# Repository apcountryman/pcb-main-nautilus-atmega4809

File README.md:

# pcb-main-nautilus-atmega4809

A Microchip ATmega4809 based mainboard PCB that uses a form factor similar to the Arduino
Uno Rev3.

## Obtaining the Source Code
HTTPS:
```shell
git clone --recurse-submodules https://github.com/apcountryman/pcb-main-nautilus-atmega4809.git
```
SSH:
```shell
git clone --recurse-submodules git@github.com:apcountryman/pcb-main-nautilus-atmega4809.git
```

## Board Setup
The board setup uses OSH Park's 4 layer board stackup and design rules which can be found
at https://docs.oshpark.com/services/ and https://docs.oshpark.com/services/four-layer/.

## Usage
This repository's Git `pre-commit` hook script is the simplest way to test this project
during development.
See the `pre-commit` script's help text for usage details.
```shell
./git/hooks/pre-commit --help
```

Additional checks, such as static analysis, are performed by this project's GitHub Actions
CI workflow.

## Versioning
`pcb-main-nautilus-atmega4809` uses [Semantic Versioning
2.0.0](https://semver.org/spec/v2.0.0.html).
Version tags are prefixed with a `v`.

## Workflow
`pcb-main-nautilus-atmega4809` uses the [GitHub
flow](https://guides.github.com/introduction/flow/) workflow.

## Git Hooks
To install this repository's Git hooks, execute the `install` script located in the
`git/hooks` directory.
See the `install` script's help text for usage details.
```shell
./git/hooks/install --help
```

## Code of Conduct
`pcb-main-nautilus-atmega4809` has adopted the Contributor Covenant 2.0 code of conduct.
For more information, [see the `CODE_OF_CONDUCT.md` file in this
repository](CODE_OF_CONDUCT.md).

## Contributing
If you are interested in contributing to `pcb-main-nautilus-atmega4809`, please [read the
`CONTRIBUTING.md` file in this repository](CONTRIBUTING.md).

## Authors
- Andrew Countryman

## License
For licensing information, [see the `LICENSE.md` file in this repository](LICENSE.md).

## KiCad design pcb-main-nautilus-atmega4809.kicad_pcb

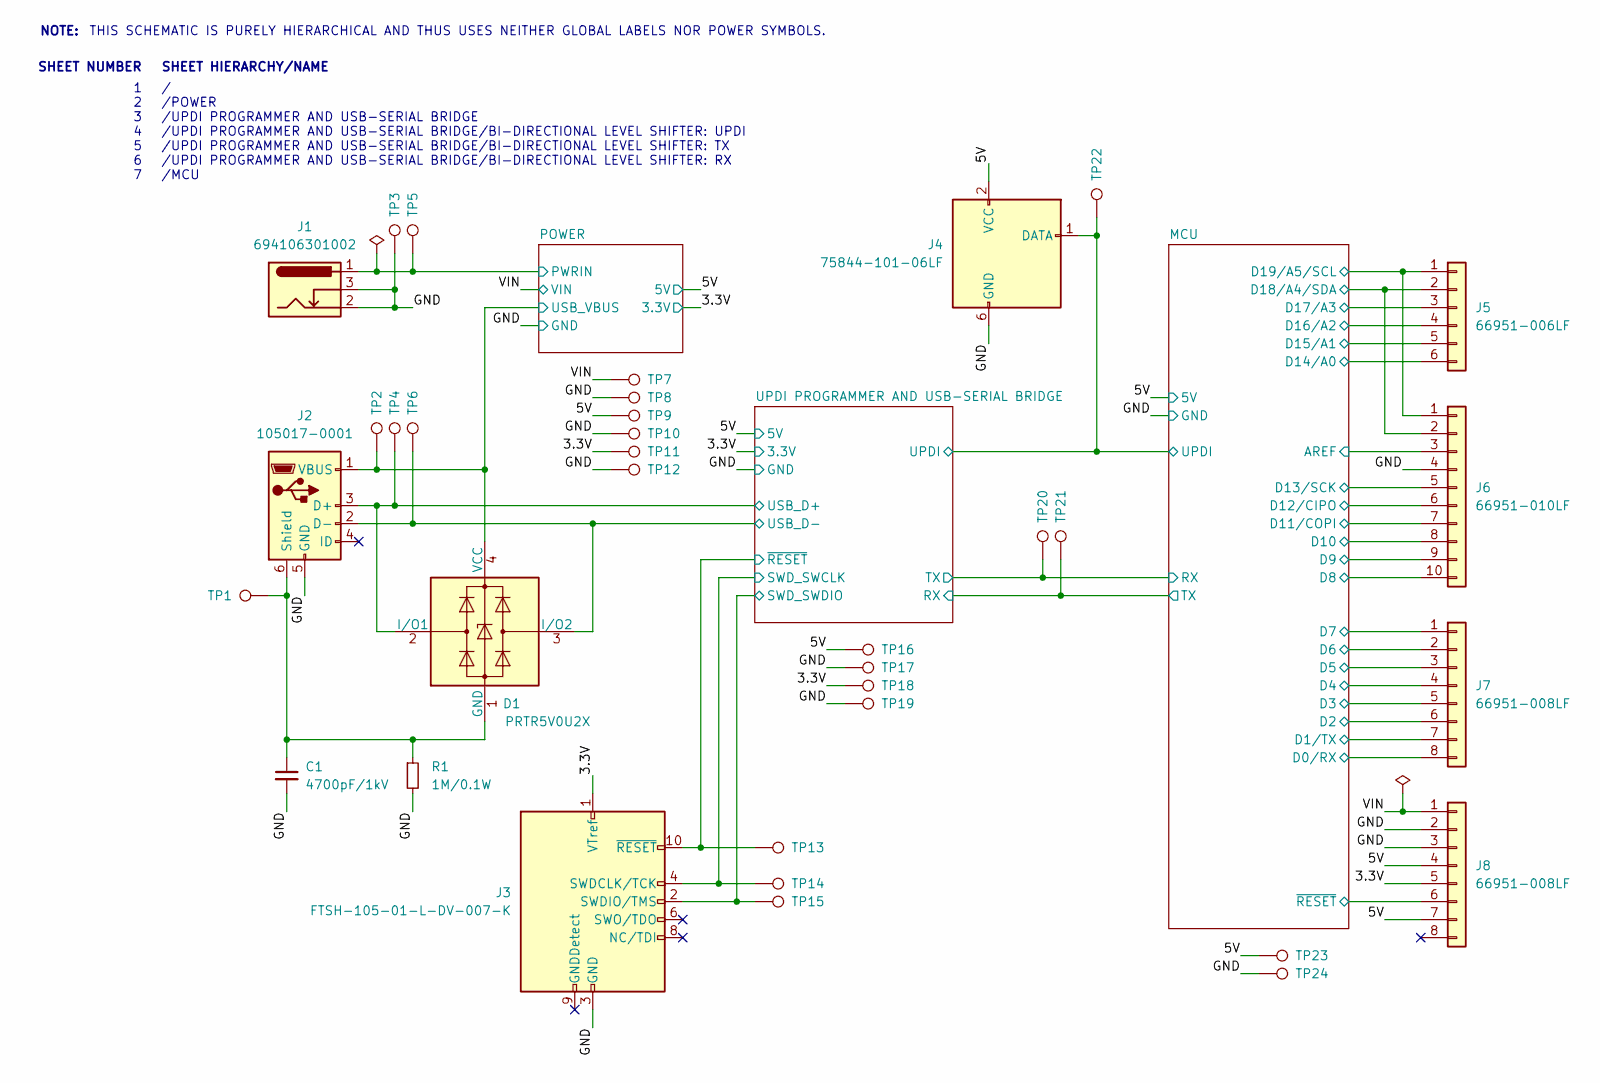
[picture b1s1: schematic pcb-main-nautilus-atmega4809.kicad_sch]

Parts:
C1: 4700pF/1kV; C_0805_2012Metric_Pad1.18x1.45mm_HandSolder; Manufacturer Part Number C0805V472KDRAC; Digi-Key Part Number 399-C0805V472KDRAC7800CT-ND
D1: PRTR5V0U2X; SOT-143; Manufacturer Part Number PRTR5V0U2X; Digi-Key Part Number 1727-3884-1-ND
J1: 694106301002; BarrelJack_Wuerth_6941xx301002; Manufacturer Part Number 694106301002; Digi-Key Part Number 732-5930-ND
J2: 105017-0001; USB_Micro-B_Molex-105017-0001; Manufacturer Part Number 105017-0001; Digi-Key Part Number WM1399CT-ND
J3: FTSH-105-01-L-DV-007-K; PinHeader_2x05_P1.27mm_Vertical_SMD; Manufacturer Part Number FTSH-105-01-L-DV-007-K; Digi-Key Part Number SAM9438-ND
J4: 75844-101-06LF; PinHeader_2x03_P2.54mm_Vertical; Manufacturer Part Number 75844-101-06LF; Digi-Key Part Number 609-75844-101-06LF-ND
J5: 66951-006LF; PinHeader_1x06_P2.54mm_Vertical; Manufacturer Part Number 66951-006LF; Digi-Key Part Number 609-2236-ND
J6: 66951-010LF; PinHeader_1x10_P2.54mm_Vertical; Manufacturer Part Number 66951-010LF; Digi-Key Part Number 609-2240-ND
J7, J8: 66951-008LF; PinHeader_1x08_P2.54mm_Vertical; Manufacturer Part Number 66951-008LF; Digi-Key Part Number 609-2238-ND
R1: 1M/0.1W; R_0603_1608Metric_Pad0.98x0.95mm_HandSolder; Manufacturer Part Number ERJ-3EKF1004; Digi-Key Part Number P1.00MHCT-ND
TP1, TP2, TP3, TP4, TP5, TP6, TP7, TP8, TP9, TP10, TP11, TP12, TP13, TP14, TP15, TP16, TP17, TP18, TP19, TP20, TP21, TP22, TP23, TP24: TestPoint; TestPoint_Pad_D1.0mm

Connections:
/3.3V: J3.1 (VTref), J8.5, TP11.1, TP18.1; also elsewhere on the board
/5V: J4.2 (VCC), J8.4, J8.7, TP9.1, TP16.1, TP23.1; also elsewhere on the board
/GND: C1.2, J1.2, J1.3, J2.5 (GND), J3.3 (GND), J3.5 (GND), J4.6 (GND), J6.4, J8.2, J8.3, R1.2, TP3.1, TP8.1, TP10.1, TP12.1, TP17.1, TP19.1, TP24.1; also elsewhere on the board
/MCU/AREF: J6.3; also elsewhere on the board
/MCU/D0/RX: J7.8; also elsewhere on the board
/MCU/D1/TX: J7.7; also elsewhere on the board
/MCU/D2: J7.6; also elsewhere on the board
/MCU/D3: J7.5; also elsewhere on the board
/MCU/D4: J7.4; also elsewhere on the board
/MCU/D5: J7.3; also elsewhere on the board
/MCU/D6: J7.2; also elsewhere on the board
/MCU/D7: J7.1; also elsewhere on the board
/MCU/D8: J6.10; also elsewhere on the board
/MCU/D9: J6.9; also elsewhere on the board
/MCU/D10: J6.8; also elsewhere on the board
/MCU/D11/COPI: J6.7; also elsewhere on the board
/MCU/D12/CIPO: J6.6; also elsewhere on the board
/MCU/D13/SCK: J6.5; also elsewhere on the board
/MCU/D14/A0: J5.6; also elsewhere on the board
/MCU/D15/A1: J5.5; also elsewhere on the board
/MCU/D16/A2: J5.4; also elsewhere on the board
/MCU/D17/A3: J5.3; also elsewhere on the board
/MCU/D18/A4/SDA: J5.2, J6.2; also elsewhere on the board
/MCU/D19/A5/SCL: J5.1, J6.1; also elsewhere on the board
/MCU/RX: TP20.1; also elsewhere on the board
/MCU/TX: TP21.1; also elsewhere on the board
/MCU/UPDI: J4.1 (DATA), TP22.1; also elsewhere on the board
/MCU/~RESET: J8.6; also elsewhere on the board
/POWER/PWRIN: J1.1, TP5.1; also elsewhere on the board
/POWER/USB_VBUS: D1.4 (VCC), J2.1 (VBUS), TP2.1; also elsewhere on the board
/UPDI PROGRAMMER AND USB-SERIAL BRIDGE/SWD_SWCLK: J3.4 (SWDCLK/TCK), TP14.1; also elsewhere on the board
/UPDI PROGRAMMER AND USB-SERIAL BRIDGE/SWD_SWDIO: J3.2 (SWDIO/TMS), TP15.1; also elsewhere on the board
/UPDI PROGRAMMER AND USB-SERIAL BRIDGE/USB_D+: D1.2 (I/O1), J2.3 (D+), TP4.1; also elsewhere on the board
/UPDI PROGRAMMER AND USB-SERIAL BRIDGE/USB_D-: D1.3 (I/O2), J2.2 (D-), TP6.1; also elsewhere on the board
/UPDI PROGRAMMER AND USB-SERIAL BRIDGE/~RESET: J3.10 (~RESET), TP13.1; also elsewhere on the board
/VIN: J8.1, TP7.1; also elsewhere on the board
unnamed: C1.1, D1.1 (GND), J2.6 (Shield), R1.1, TP1.1

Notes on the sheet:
/ /POWER /UPDI PROGRAMMER AND USB-SERIAL BRIDGE /UPDI PROGRAMMER AND USB-SERIAL BRIDGE/BI-DIRECTIONAL LEVEL SHIFTER: UPDI /UPDI PROGRAMMER AND USB-SERIAL BRIDGE/BI-DIRECTIONAL LEVEL SHIFTER: TX /UPDI PROGRAMMER AND USB-SERIAL BRIDGE/BI-DIRECTIONAL LEVEL SHIFTER: RX /MCU
SHEET HIERARCHY/NAME
1 2 3 4 5 6 7
THIS SCHEMATIC IS PURELY HIERARCHICAL AND THUS USES NEITHER GLOBAL LABELS NOR POWER SYMBOLS.
SHEET NUMBER
NOTE:

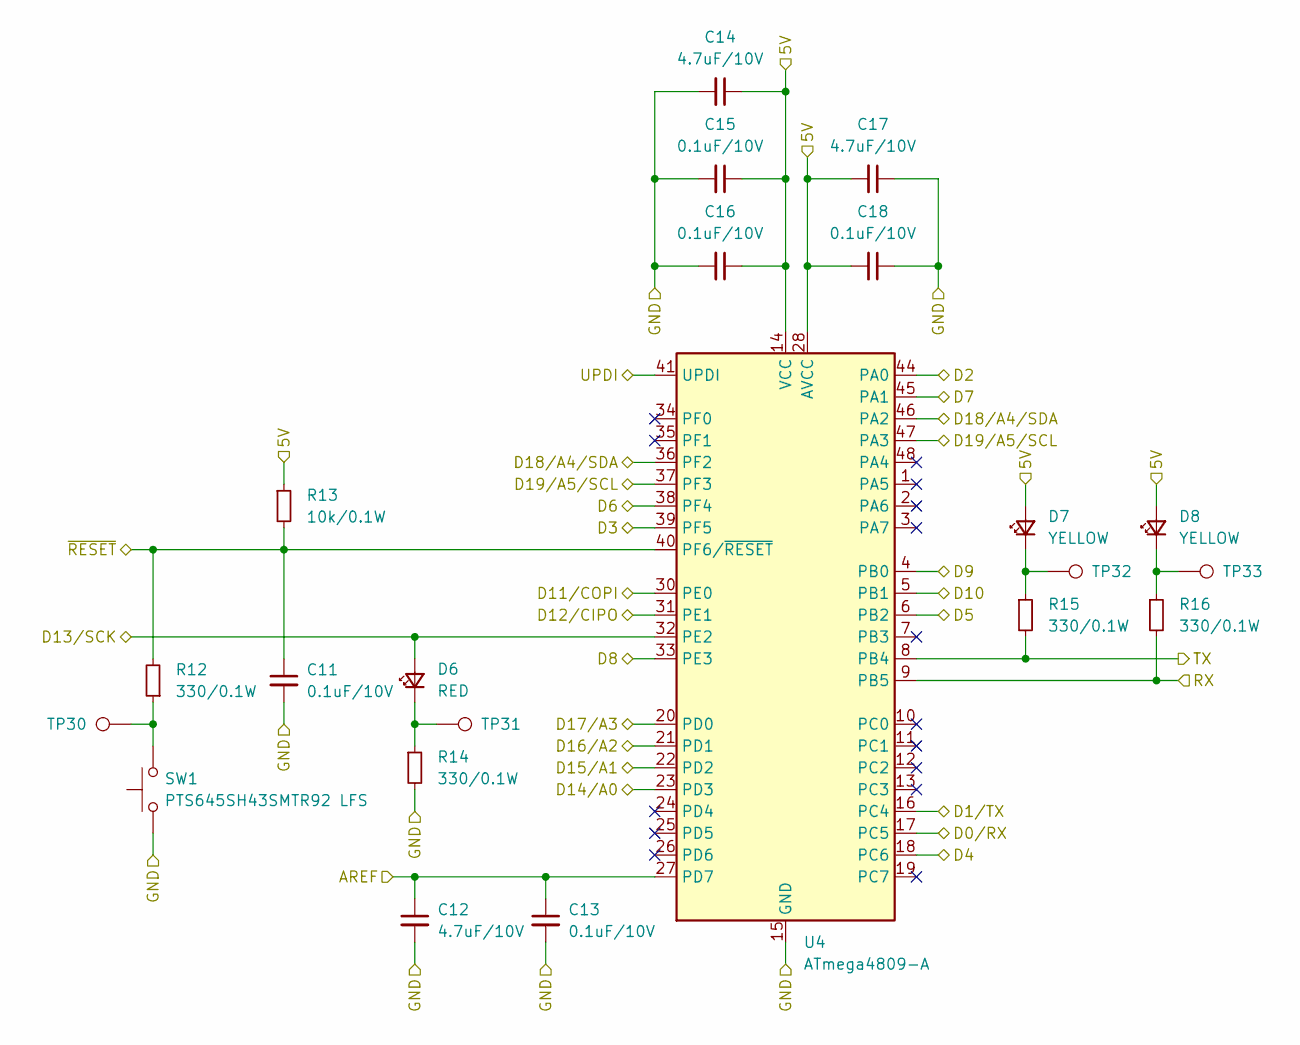
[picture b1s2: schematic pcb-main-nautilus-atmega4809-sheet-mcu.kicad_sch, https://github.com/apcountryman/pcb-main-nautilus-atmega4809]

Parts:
C11, C13, C15, C16, C18: 0.1uF/10V; C_0603_1608Metric_Pad1.08x0.95mm_HandSolder; Manufacturer Part Number C0603C104M8RAC; Digi-Key Part Number 399-C0603C104M8RAC7867CT-ND
C12, C14, C17: 4.7uF/10V; C_0603_1608Metric_Pad1.08x0.95mm_HandSolder; Manufacturer Part Number C0603C475M8PAC; Digi-Key Part Number 399-C0603C475M8PAC7867CT-ND
D6: RED; LED_0603_1608Metric_Pad1.05x0.95mm_HandSolder; Manufacturer Part Number LTST-C190KRKT; Digi-Key Part Number 160-1436-1-ND
D7, D8: YELLOW; LED_0603_1608Metric_Pad1.05x0.95mm_HandSolder; Manufacturer Part Number LTST-C190KSKT; Digi-Key Part Number 160-1437-1-ND
R12, R14, R15, R16: 330/0.1W; R_0603_1608Metric_Pad0.98x0.95mm_HandSolder; Manufacturer Part Number ERJ-3EKF3300; Digi-Key Part Number P330HCT-ND
R13: 10k/0.1W; R_0603_1608Metric_Pad0.98x0.95mm_HandSolder; Manufacturer Part Number ERJ-3EKF1002; Digi-Key Part Number P10.0KHCT-ND
SW1: PTS645SH43SMTR92 LFS; SW_Push_1P1T_NO_6x6mm_H9.5mm; Manufacturer Part Number PTS645SH43SMTR92 LFS; Digi-Key Part Number CKN11907CT-ND
TP30, TP31, TP32, TP33: TestPoint; TestPoint_Pad_D1.0mm
U4: ATmega4809-A; TQFP-48_7x7mm_P0.5mm; Manufacturer Part Number ATMEGA4809-AU; Digi-Key Part Number 150-ATMEGA4809-AURCT-ND

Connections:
/5V: C14.1, C15.1, C16.1, C17.2, C18.2, D7.2 (A), D8.2 (A), R13.1, U4.14 (VCC), U4.28 (AVCC), U4.42 (VCC); also elsewhere on the board
/GND: C11.2, C12.2, C13.2, C14.2, C15.2, C16.2, C17.1, C18.1, R14.2, SW1.1, U4.15 (GND), U4.29 (GND), U4.43 (GND); also elsewhere on the board
/MCU/AREF: C12.1, C13.1, U4.27 (PD7); also elsewhere on the board
/MCU/D0/RX: U4.17 (PC5); also elsewhere on the board
/MCU/D1/TX: U4.16 (PC4); also elsewhere on the board
/MCU/D2: U4.44 (PA0); also elsewhere on the board
/MCU/D3: U4.39 (PF5); also elsewhere on the board
/MCU/D4: U4.18 (PC6); also elsewhere on the board
/MCU/D5: U4.6 (PB2); also elsewhere on the board
/MCU/D6: U4.38 (PF4); also elsewhere on the board
/MCU/D7: U4.45 (PA1); also elsewhere on the board
/MCU/D8: U4.33 (PE3); also elsewhere on the board
/MCU/D9: U4.4 (PB0); also elsewhere on the board
/MCU/D10: U4.5 (PB1); also elsewhere on the board
/MCU/D11/COPI: U4.30 (PE0); also elsewhere on the board
/MCU/D12/CIPO: U4.31 (PE1); also elsewhere on the board
/MCU/D13/SCK: D6.2 (A), U4.32 (PE2); also elsewhere on the board
/MCU/D14/A0: U4.23 (PD3); also elsewhere on the board
/MCU/D15/A1: U4.22 (PD2); also elsewhere on the board
/MCU/D16/A2: U4.21 (PD1); also elsewhere on the board
/MCU/D17/A3: U4.20 (PD0); also elsewhere on the board
/MCU/D18/A4/SDA: U4.36 (PF2), U4.46 (PA2); also elsewhere on the board
/MCU/D19/A5/SCL: U4.37 (PF3), U4.47 (PA3); also elsewhere on the board
/MCU/RX: R16.2, U4.9 (PB5); also elsewhere on the board
/MCU/TX: R15.2, U4.8 (PB4); also elsewhere on the board
/MCU/UPDI: U4.41 (UPDI); also elsewhere on the board
/MCU/~RESET: C11.1, R12.2, R13.2, U4.40 (PF6/~RESET); also elsewhere on the board
unnamed: D6.1 (K), R14.1, TP31.1
unnamed: D7.1 (K), R15.1, TP32.1
unnamed: D8.1 (K), R16.1, TP33.1
unnamed: R12.1, SW1.2, TP30.1

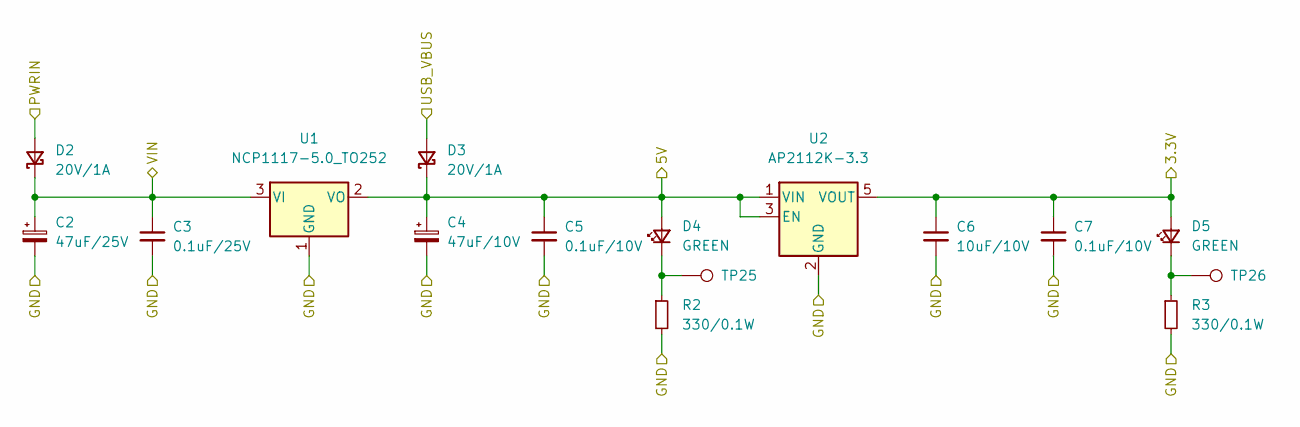
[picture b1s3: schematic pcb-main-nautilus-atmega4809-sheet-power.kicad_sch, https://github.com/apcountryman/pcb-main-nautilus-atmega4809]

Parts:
C2: 47uF/25V; CP_Elec_6.3x7.7; Manufacturer Part Number EEEHC1E470XP; Digi-Key Part Number PCE3753CT-ND
C3: 0.1uF/25V; C_0603_1608Metric_Pad1.08x0.95mm_HandSolder; Manufacturer Part Number C0603C104M3RAC; Digi-Key Part Number 399-C0603C104M3RAC7867CT-ND
C4: 47uF/10V; CP_Elec_4x5.8; Manufacturer Part Number EEEFN1A470UR; Digi-Key Part Number 10-EEE-FN1A470URCT-ND
C5, C7: 0.1uF/10V; C_0603_1608Metric_Pad1.08x0.95mm_HandSolder; Manufacturer Part Number C0603C104M8RAC; Digi-Key Part Number 399-C0603C104M8RAC7867CT-ND
C6: 10uF/10V; C_0603_1608Metric_Pad1.08x0.95mm_HandSolder; Manufacturer Part Number C0603C106M8PAC; Digi-Key Part Number 399-14945-1-ND
D2, D3: 20V/1A; D_SOD-123F; Manufacturer Part Number MBR120LSF; Digi-Key Part Number MBR120LSFT3GOSCT-ND
D4, D5: GREEN; LED_0603_1608Metric_Pad1.05x0.95mm_HandSolder; Manufacturer Part Number LTST-C190KGKT; Digi-Key Part Number 160-1435-1-ND
R2, R3: 330/0.1W; R_0603_1608Metric_Pad0.98x0.95mm_HandSolder; Manufacturer Part Number ERJ-3EKF3300; Digi-Key Part Number P330HCT-ND
TP25, TP26: TestPoint; TestPoint_Pad_D1.0mm
U1: NCP1117-5.0_TO252; TO-252-2; Manufacturer Part Number NCP1117DT50; Digi-Key Part Number NCP1117DT50RKGOSCT-ND
U2: AP2112K-3.3; SOT-23-5; Manufacturer Part Number AP2112K-3.3TRG1; Digi-Key Part Number AP2112K-3.3TRG1DICT-ND

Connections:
/3.3V: C6.1, C7.1, D5.2 (A), U2.5 (VOUT); also elsewhere on the board
/5V: C4.1, C5.1, D3.1 (K), D4.2 (A), U1.2 (VO), U2.1 (VIN), U2.3 (EN); also elsewhere on the board
/GND: C2.2, C3.2, C4.2, C5.2, C6.2, C7.2, R2.2, R3.2, U1.1 (GND), U2.2 (GND); also elsewhere on the board
/POWER/PWRIN: D2.2 (A); also elsewhere on the board
/POWER/USB_VBUS: D3.2 (A); also elsewhere on the board
/VIN: C2.1, C3.1, D2.1 (K), U1.3 (VI); also elsewhere on the board
unnamed: D4.1 (K), R2.1, TP25.1
unnamed: D5.1 (K), R3.1, TP26.1

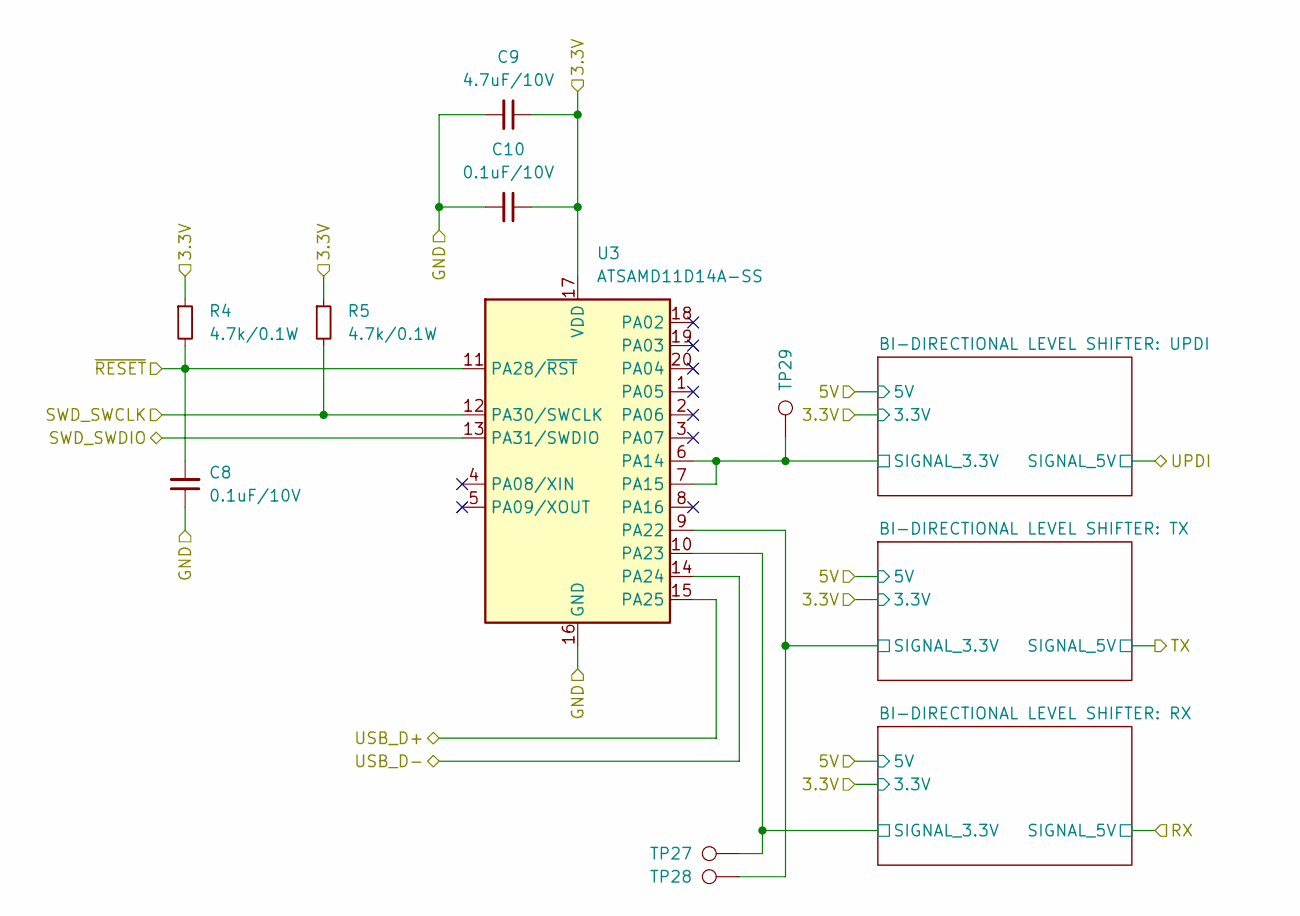
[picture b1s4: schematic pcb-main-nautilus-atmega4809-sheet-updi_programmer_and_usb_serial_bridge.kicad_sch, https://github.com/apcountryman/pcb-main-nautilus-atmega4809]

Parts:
C8, C10: 0.1uF/10V; C_0603_1608Metric_Pad1.08x0.95mm_HandSolder; Manufacturer Part Number C0603C104M8RAC; Digi-Key Part Number 399-C0603C104M8RAC7867CT-ND
C9: 4.7uF/10V; C_0603_1608Metric_Pad1.08x0.95mm_HandSolder; Manufacturer Part Number C0603C475M8PAC; Digi-Key Part Number 399-C0603C475M8PAC7867CT-ND
R4, R5: 4.7k/0.1W; R_0603_1608Metric_Pad0.98x0.95mm_HandSolder; Manufacturer Part Number ERJ-3EKF4701; Digi-Key Part Number P4.70KHCT-ND
TP27, TP28, TP29: TestPoint; TestPoint_Pad_D1.0mm
U3: ATSAMD11D14A-SS; SOIC-20W_7.5x12.8mm_P1.27mm; Manufacturer Part Number ATSAMD11D14A-SSU; Digi-Key Part Number ATSAMD11D14A-SSUTCT-ND

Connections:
/3.3V: C9.1, C10.1, R4.1, R5.1, U3.17 (VDD); also elsewhere on the board
/GND: C8.1, C9.2, C10.2, U3.16 (GND); also elsewhere on the board
/UPDI PROGRAMMER AND USB-SERIAL BRIDGE/BI-DIRECTIONAL LEVEL SHIFTER: RX/SIGNAL_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: TP27.1, U3.10 (PA23); also elsewhere on the board
/UPDI PROGRAMMER AND USB-SERIAL BRIDGE/BI-DIRECTIONAL LEVEL SHIFTER: TX/SIGNAL_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: TP28.1, U3.9 (PA22); also elsewhere on the board
/UPDI PROGRAMMER AND USB-SERIAL BRIDGE/BI-DIRECTIONAL LEVEL SHIFTER: UPDI/SIGNA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: TP29.1, U3.6 (PA14), U3.7 (PA15); also elsewhere on the board
/UPDI PROGRAMMER AND USB-SERIAL BRIDGE/SWD_SWCLK: R5.2, U3.12 (PA30/SWCLK); also elsewhere on the board
/UPDI PROGRAMMER AND USB-SERIAL BRIDGE/SWD_SWDIO: U3.13 (PA31/SWDIO); also elsewhere on the board
/UPDI PROGRAMMER AND USB-SERIAL BRIDGE/USB_D+: U3.15 (PA25); also elsewhere on the board
/UPDI PROGRAMMER AND USB-SERIAL BRIDGE/USB_D-: U3.14 (PA24); also elsewhere on the board
/UPDI PROGRAMMER AND USB-SERIAL BRIDGE/~RESET: C8.2, R4.2, U3.11 (PA28/~RST); also elsewhere on the board

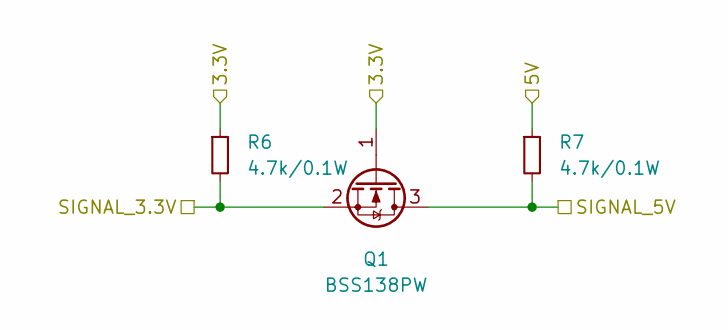
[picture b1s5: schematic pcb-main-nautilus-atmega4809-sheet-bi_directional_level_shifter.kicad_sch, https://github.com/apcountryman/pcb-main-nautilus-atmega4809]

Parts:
Q1: BSS138PW; SOT-323_SC-70_Handsoldering; Manufacturer Part Number BSS138PW; Digi-Key Part Number 1727-1143-1-ND
R6, R7: 4.7k/0.1W; R_0603_1608Metric_Pad0.98x0.95mm_HandSolder; Manufacturer Part Number ERJ-3EKF4701; Digi-Key Part Number P4.70KHCT-ND

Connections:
/3.3V: Q1.1 (G), R6.1; also elsewhere on the board
/5V: R7.1; also elsewhere on the board
/MCU/UPDI: Q1.3 (D), R7.2; also elsewhere on the board
/UPDI PROGRAMMER AND USB-SERIAL BRIDGE/BI-DIRECTIONAL LEVEL SHIFTER: UPDI/SIGNA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: Q1.2 (S), R6.2; also elsewhere on the board

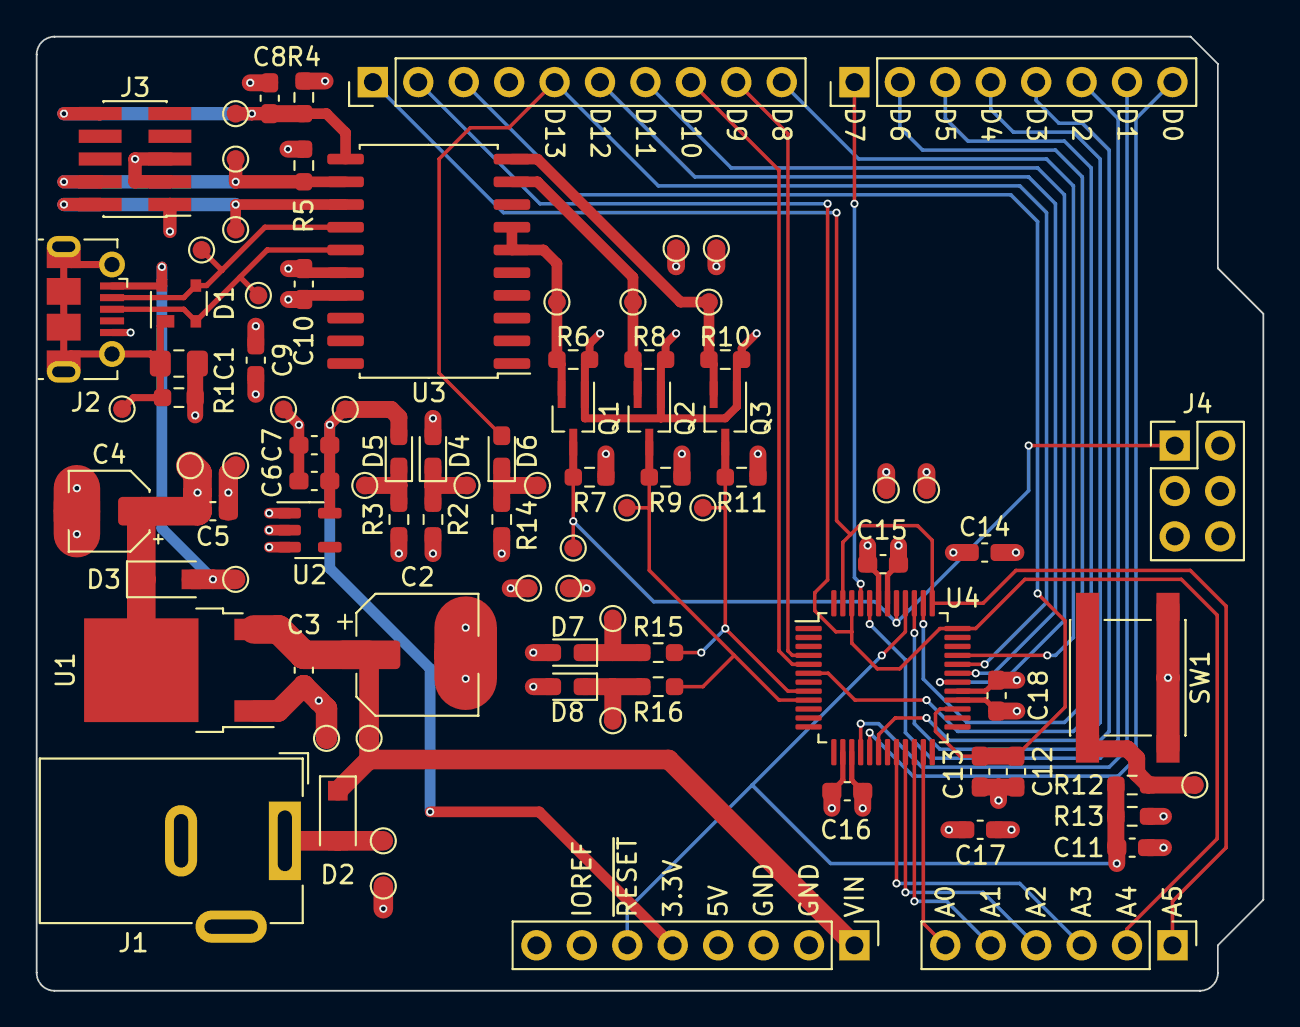
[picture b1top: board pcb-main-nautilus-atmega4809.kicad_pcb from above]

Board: 4 copper layers, 68.6 x 53.3 mm, 91 parts (0 on the bottom side), 46 nets.

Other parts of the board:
Q2, Q3: BSS138PW; SOT-323_SC-70_Handsoldering
R8, R9, R10, R11: 4.7k/0.1W; R_0603_1608Metric_Pad0.98x0.95mm_HandSolder

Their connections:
/3.3V: Q2.1 (G), Q3.1 (G), R8.1, R10.1; also elsewhere on the board
/5V: R9.1, R11.1; also elsewhere on the board
/MCU/RX: Q2.3 (D), R9.2; also elsewhere on the board
/MCU/TX: Q3.3 (D), R11.2; also elsewhere on the board
/UPDI PROGRAMMER AND USB-SERIAL BRIDGE/BI-DIRECTIONAL LEVEL SHIFTER: RX/SIGNAL_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: Q3.2 (S), R10.2; also elsewhere on the board
/UPDI PROGRAMMER AND USB-SERIAL BRIDGE/BI-DIRECTIONAL LEVEL SHIFTER: TX/SIGNAL_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: Q2.2 (S), R8.2; also elsewhere on the board

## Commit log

2022-10-13 Add schematic
    Resolves #1 (Add schematic).
2022-10-13 Add schematic skeleton
    Supports #2.
2022-10-13 Update CI job dependencies
    Supports #2.
2022-10-15 Populate revision in generated files
    Supports #2.
2022-10-26 Add ignore rules for generated files
    Supports #2.
2022-10-26 Add schematic restoration to CI scripts
    Supports #2.
2022-10-26 Add additional traditional BOM file formats
    Supports #2.
2022-10-26 Fix CI job dependencies
    Supports #2.
2022-10-26 Add KiBoM configuration
    Supports #2.
2022-10-27 Add power sheet
    Supports #2.
2022-10-28 Treat additional ERC findings as errors
    Supports #2.
2022-10-28 Add UPDI programmer and USB-serial bridge sheet
    Supports #2.
2022-10-29 Add bi-directional level shifter sheet
    Supports #2.
2022-10-29 Capitalize sheet names
    Supports #2.
2022-10-29 Fix datasheet link
    Supports #2.
2022-10-29 Add electrolytic capacitor footprints
    Supports #2.
2022-10-29 Update ignore rules
    Supports #2.
2022-10-29 Add filename to sheet
    Supports #2.
2022-10-29 Fix missing part info
    Supports #2.
2022-10-29 Add nettie footprint
    Supports #2.
2022-10-29 Remove nettie from BOM
    Supports #2.
2022-10-29 Update KiBoB configuration
    Supports #2.
2022-10-30 Replace Digi-Key part numbers with links
    Supports #2.
2022-10-30 Replace Mouser part numbers with links
    Supports #2.
2022-10-30 Fix manufacturer name
    Supports #2.
2022-10-30 Add MCU sheet
    Supports #2.
2022-10-30 Annotate schematic
    Supports #2.
2022-10-30 Add nettie footprints
    Supports #2.
2022-10-31 Add D13 LED
    Supports #2.
2022-10-31 Add serial LEDs
    Supports #2.
2022-10-31 Add MCU reset circuit
    Supports #2.
2022-10-31 Switch to generated Digi-Key and Mouser links
    Supports #2.
2022-10-31 Fix serial activity LEDs wiring
    Supports #2.
2022-10-31 Improve MCU sheet flow
    Supports #2.
2022-10-31 Improve UDPI programmer and USB-serial bridge sheet flow
    Supports #2.
2022-10-31 Update KiBoM
    Supports #2.
2022-10-31 Update schematic annotations
    Supports #2.
2022-11-01 Connect root sheet
    Supports #2.
2022-11-01 Nest level shifter sheets under UPDI programmer and bridge sheet
    Supports #2.
2022-11-01 Serialize power sheet
    Supports #2.
2022-11-01 Add power flags
    Supports #2.
2022-11-01 Fix style inconsistencies
    Supports #2.
2022-11-01 Fix NetTie usage
    Supports #2.
2022-11-01 Rename serial signals
    Supports #2.
2022-11-01 Reduce ~{RESET} pull-up strength
    Supports #2.
2022-11-01 Revise 3.3 V rail bulk capacitor rating
    Supports #2.
2022-11-01 Revise CI generated file names
    Supports #2.
2022-11-01 Remove filenames from layout
    Supports #2.
2022-11-01 Reorder traditional BOM fields
    Supports #2.
2022-11-01 Update BOM
    Supports #2.
2022-11-01 Add sheet decoder
    Supports #2.
2022-11-21 Fix version population
    Supports #2.
2022-11-21 Add logging to CI jobs to debug unknown Git SHA
    Supports #2.
2022-11-21 Revert "Add logging to CI jobs to debug unknown Git SHA"
    This reverts commit 88c5827e12055bafa5853510f295e554c31800ba.
    Supports #2.
    Unknown Git SHA is due to a merge being performed as part of the CI
    jobs.
2022-11-21 Remove improperly used netties
    Supports #2.
2022-11-22 Hide power flag values
    Supports #2.
2022-11-28 Add test points
    Supports #2.
2022-12-01 Address review findings
    Supports #2.
2022-12-01 Add schematic (#2)
    Resolves #1 (Add schematic).
2022-12-18 Add layout
    Resolves #3 (Add layout).
2022-12-19 Add design rules compliance check CI script/job
    Supports #4.
2022-12-19 Adjust design rule violation severity
    Supports #4.
2023-01-16 Configure board stackup
    Supports #4.
2023-01-16 Configure constraints
    Supports #4.
2023-01-16 Configure default net class
    Supports #4.
2023-01-16 Document board setup source
    Supports #4.
2023-01-21 Fix use of wrong symbol
    Supports #4.
2023-02-09 Move components to edge of work area
    Supports #4.
2023-02-09 Add board outline
    Supports #4.
2023-02-09 Place headers and power connector
    Supports #4.
2023-02-10 Lock board outline, headers, and power connector
    Supports #4.
2023-02-15 Place USB connector
    Supports #4.
2023-02-15 Group components
    Supports #4.
2023-02-15 Add missing test points
    Supports #4.
2023-02-27 Arrange USB programmer and USB-serial bridge components
    Supports #4.
2023-02-28 Arrange microcontroller decoupling capacitors
    Supports #4.
2023-02-28 Remove unnecessary test points
    Supports #4.
2023-02-28 Arrange power indicators
    Supports #4.
2023-02-28 Arrange TX/RX indicators
    Supports #4.
2023-02-28 Arrange user indicator
    Supports #4.
2023-02-28 Add planes
    Supports #4.
2023-02-28 Hide header reference designators
    Supports #4.
2023-02-28 Place USB support components
    Supports #4.
2023-03-01 Reduce board edge line width
    Supports #4.
2023-03-01 Adjust connector placement to avoid silk DRC errors
    Supports #4.
2023-03-01 Place 5 V power circuitry
    Supports #4.
2023-03-01 Place UPDI programmer and USB-serial bridge circuitry
    Supports #4.
2023-03-06 Finish place and route
    Supports #4.
2023-03-07 Add header pin labels
    Supports #4.
2023-03-07 Add board info silk
    Supports #4.
2023-03-20 Add origin
    Supports #4.
2023-03-20 Update KiAuto
    Supports #4.
2023-03-20 Update KiBom
    Supports #4.
2023-03-20 Force GUI use for DRC check
    Supports #4.
2023-03-20 Add interactive BOM generation
    Supports #4.
2023-03-20 Fix interactive BOM generation dependencies installation
    Supports #4.
2023-03-20 Fix interactive BOM generation
    Supports #4.
2023-03-20 Adjust interactive BOM generation
    Supports #4.
2023-03-20 Add production files generation
    Supports #4.
2023-03-20 Fix typo
    Supports #4.
2023-03-20 Add PCB renders generation
    Supports #4.
2023-03-20 Fix PcbDraw usage
    Supports #4.
2023-03-21 Remove PCB renders generation
    Supports #4.
2023-03-23 Address review findings
    Supports #4.
2023-03-23 Add layout (#4)
    Resolves #3 (Add layout).
2023-03-23 Update copyright dates
    Resolves #5 (Update copyright dates).
2023-03-23 Update copyright dates (#6)
    Resolves #5 (Update copyright dates).
2023-03-27 Update actions/checkout to v3
    Resolves #8 (Update actions/checkout to v3).
2023-03-27 Update actions/checkout to v3 (#10)
    Resolves #8 (Update actions/checkout to v3).
2023-03-27 Update actions/upload-artifact to v3
    Resolves #9 (Update actions/upload-artifact to v3).
2023-03-27 Update actions/upload-artifact to v3 (#11)
    Resolves #9 (Update actions/upload-artifact to v3).
2023-03-30 Add release generation
    Resolves #7 (Add release generation).
2023-03-31 Update version population
    Supports #12.
2023-03-31 Overhaul CD release generation script
    Supports #12.
2023-03-31 Add release generation (#12)
    Resolves #7 (Add release generation).
2023-03-31 Fix interactive BOM archival
    Resolves #13 (Fix interactive BOM archival).
2023-03-31 Fix interactive BOM archival (#14)
    Resolves #13 (Fix interactive BOM archival).
2023-03-31 Fix production files archival
    Resolves #15 (Fix production files archival).
2023-03-31 Fix production files archival (#16)
    Resolves #15 (Fix production files archival).
2023-03-31 Fix release upload
    Resolves #17 (Fix release upload).
2023-03-31 Fix release upload (#18)
    Resolves #17 (Fix release upload).
2023-03-31 Revise CD workflow triggers
    Resolves #19 (Revise CD workflow triggers).
2023-03-31 Revise CD workflow triggers (#20)
    Resolves #19 (Revise CD workflow triggers).
2023-03-31 Fix release generation script version determination
    Resolves #21 (Fix release generation script version determination).
2023-03-31 Fix release generation script version determination (#22)
    Resolves #21 (Fix release generation script version determination).
2023-04-01 Revise release archive name
    Resolves #24 (Revise release archive name).
2023-04-01 Revise release archive name (#27)
    Resolves #24 (Revise release archive name).
2023-04-01 Fix release archive file structure
    Resolves #25 (Fix release archive file structure).
2023-04-02 Fix release archive file structure (#29)
    Resolves #25 (Fix release archive file structure).
2023-04-02 Revise CI interactive BOM archive file structure
    Resolves #26 (Revise CI interactive BOM archive file structure).
2023-04-02 Revise CI interactive BOM archive file structure (#30)
    Resolves #26 (Revise CI interactive BOM archive file structure).
2023-04-02 Rename release generation CD job/script
    Resolves #28 (Rename release generation CD job/script).
2023-04-02 Rename release generation CD job/script (#31)
    Resolves #28 (Rename release generation CD job/script).
2023-04-02 Set hardware files release assert name
    Resolves #32 (Set hardware files release assert name).
2023-04-02 Set hardware files release assert name (#33)
    Resolves #32 (Set hardware files release assert name).
2023-04-02 Remove hardware files release asset name
    Resolves #34 (Remove hardware files release asset name).
    Revert "Set hardware files release assert name (#33)"
    This reverts commit d694f0532b9b04a9f78b10c7ab2c69e391a59690.
2023-04-02 Remove hardware files release asset name (#35)
    Resolves #34 (Remove hardware files release asset name).
    Revert "Set hardware files release assert name (#33)"
    This reverts commit d694f0532b9b04a9f78b10c7ab2c69e391a59690.
2023-04-04 Switch to semantic versioning
    Resolves #36 (Switch to semantic versioning).
2023-04-04 Switch to semantic versioning (#37)
    Resolves #36 (Switch to semantic versioning).
2023-04-27 Fix SWD connector footprint
    Resolves #38 (Fix SWD connector footprint).
2023-04-27 Remove unused footprint library
    Supports #39.
2023-04-27 Fix SWD connector footprint (#39)
    Resolves #38 (Fix SWD connector footprint).
2023-04-27 Add KiCad worksheet to release hardware files
    Resolves #40 (Add KiCad worksheet to release hardware files).
2023-04-27 Add KiCad worksheet to release hardware files (#41)
    Resolves #40 (Add KiCad worksheet to release hardware files).
